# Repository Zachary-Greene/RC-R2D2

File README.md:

# Mini Remote Control R2D2

This repo is for my mini remote control R2D2 project. It includes all the stl files, all the code files, and the f3z (Fusion 360) file. It also includes some Fusion 360 renders and some extra images.

## Prerequisites
All you need is access to a 3D printer, some skills with through-hole soldering and the parts needed.

## Assembly
First solder the components on to the PCB, making sure that they are the right way around and aligned with the silkscreen. Then place the main PCB in the bottom of the body. Place the motors in the mounts in the feet and push the wires through the feet and legs. Then push and glue if necessary the foot to the corresponding leg, eg left foot to left leg. Then push the legs through the holes in the body, making sure to get the in the right orientation, then push the fastening bolt through the holes to secure the legs in the correct position, then glue them. Repeat for the other leg. For the center foot, put the axle through the wheel and glue the axle in place, not the wheel. For the head mechanism, put the motor inside the head stem with the motor lock glued in place under it, then slide the head stem on to the pegs pointing upwards from the body, from there, put the head on to the head stem with some glue. You then plug the wires into the main PCB, turn it on and put the head on top. For the controller, solder the components on and enjoy. (The wheels are lego wheels as they are what I have handy from siblings and will probably be changed in the coming time.)

## Programming
Plug the ATmega328P into a programmer and burn the bootloader if it doesnt already have one. Then upload the corresponding sketch and put the IC in the proper socket.

## Parts
### Main PCB
* ATmega328P Digikey x1
* LD1117V33 (COM-00526) Sparkfun/Core Electronics x1
* NRF24L01 x1
* NPN Transistor (COM-00521) Sparkfun/Core Electronics x12
* 4xAA Battery Holder (PRT-12083) Sparkfun/Core Electronics x1
#### The following is for an optional speaker system
* 0.1uF Ceramic Capacitor (COM-08375) Sparkfun/Core Electronics x1
* 1.25K Ohm Resistor Digikey x1
* 8 Ohm Speaker x1
* DFPlayer Mini (DFR0299) Core Electronics x1

### Controller PCB
* ATmega328P Digikey x1
* LD1117V33 (COM-00526) Sparkfun/Core Electronics x1
* Thumb Joystick (COM-09032) Sparkfun/Core Electronics x2
* NRF24L01 x1
* 4xAA Battery Holder (PRT-12083) Sparkfun/Core Electronics x1

## Renders
.PNG "R2D2 2-3-2 Configuration")
.png "R2D2 2-2 Configuration")

## License
See LICENSE.md

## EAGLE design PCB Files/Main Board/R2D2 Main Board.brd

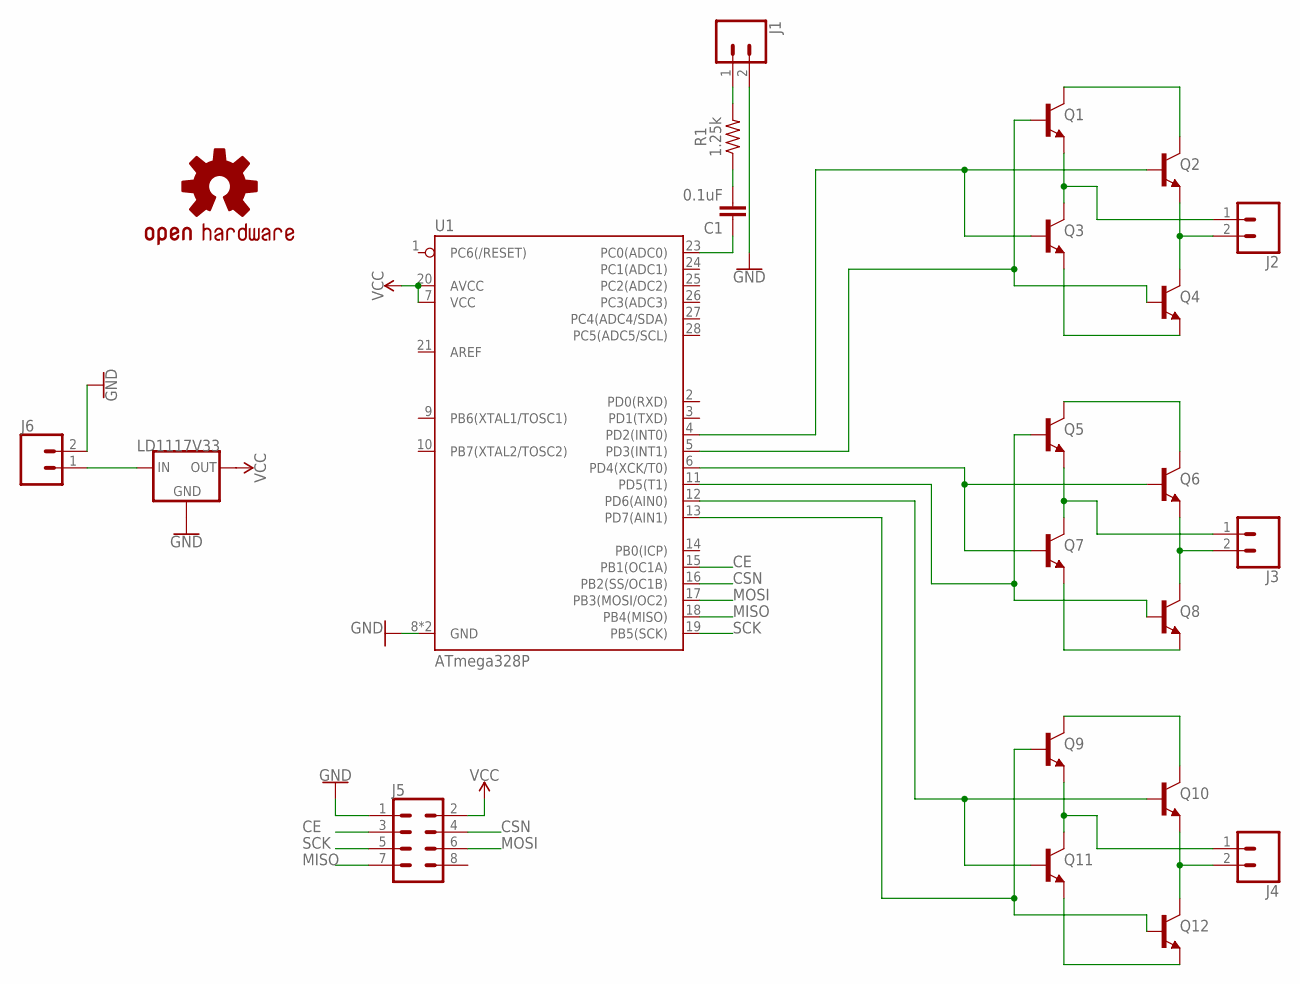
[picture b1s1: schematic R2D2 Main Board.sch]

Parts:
C1: 0.1uF; CAP-PTH-SMALL-KIT
J1, J2, J3, J4, J6: CONN_02; 1X02
J5: CONN_04X2; 2X4
LOGO1: OSHW-LOGOL; OSHW-LOGO-L
Q1, Q2, Q3, Q4, Q5, Q6, Q7, Q8, Q9, Q10, Q11, Q12: 200mA/40V; TO-92
R1: 1.25k; AXIAL-0.3
U1: ATmega328P; DIP28
U$1: LD1117V33; 78XXL

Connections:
CE: J5.3, U1.15 (PB1(OC1A))
CSN: J5.4, U1.16 (PB2(SS/OC1B))
GND: J1.2, J5.1, J6.2, U1.8 (GND), U1.22 (GND), U$1.IN (GND)
MISO: J5.7, U1.18 (PB4(MISO))
MOSI: J5.6, U1.17 (PB3(MOSI/OC2))
unnamed: Q1.3 (C), Q2.3 (C)
unnamed: Q3.1 (E), Q4.1 (E)
unnamed: J2.2, Q2.1 (E), Q4.3 (C)
unnamed: J2.1, Q1.1 (E), Q3.3 (C)
unnamed: Q2.2 (B), Q3.2 (B), U1.4 (PD2(INT0))
unnamed: Q1.2 (B), Q4.2 (B), U1.5 (PD3(INT1))
unnamed: Q5.3 (C), Q6.3 (C)
unnamed: Q7.1 (E), Q8.1 (E)
unnamed: J3.2, Q6.1 (E), Q8.3 (C)
unnamed: J3.1, Q5.1 (E), Q7.3 (C)
unnamed: Q6.2 (B), Q7.2 (B), U1.6 (PD4(XCK/T0))
unnamed: Q5.2 (B), Q8.2 (B), U1.11 (PD5(T1))
unnamed: Q9.3 (C), Q10.3 (C)
unnamed: Q11.1 (E), Q12.1 (E)
unnamed: J4.2, Q10.1 (E), Q12.3 (C)
unnamed: J4.1, Q9.1 (E), Q11.3 (C)
unnamed: Q10.2 (B), Q11.2 (B), U1.12 (PD6(AIN0))
unnamed: Q9.2 (B), Q12.2 (B), U1.13 (PD7(AIN1))
unnamed: C1.1, U1.23 (PC0(ADC0))
unnamed: C1.2, R1.P$1 (1)
unnamed: J1.1, R1.P$2 (2)
SCK: J5.5, U1.19 (PB5(SCK))
VCC: J5.2, U1.7 (VCC), U1.20 (AVCC), U$1.GND (OUT)
VIN: J6.1, U$1.OUT (IN)

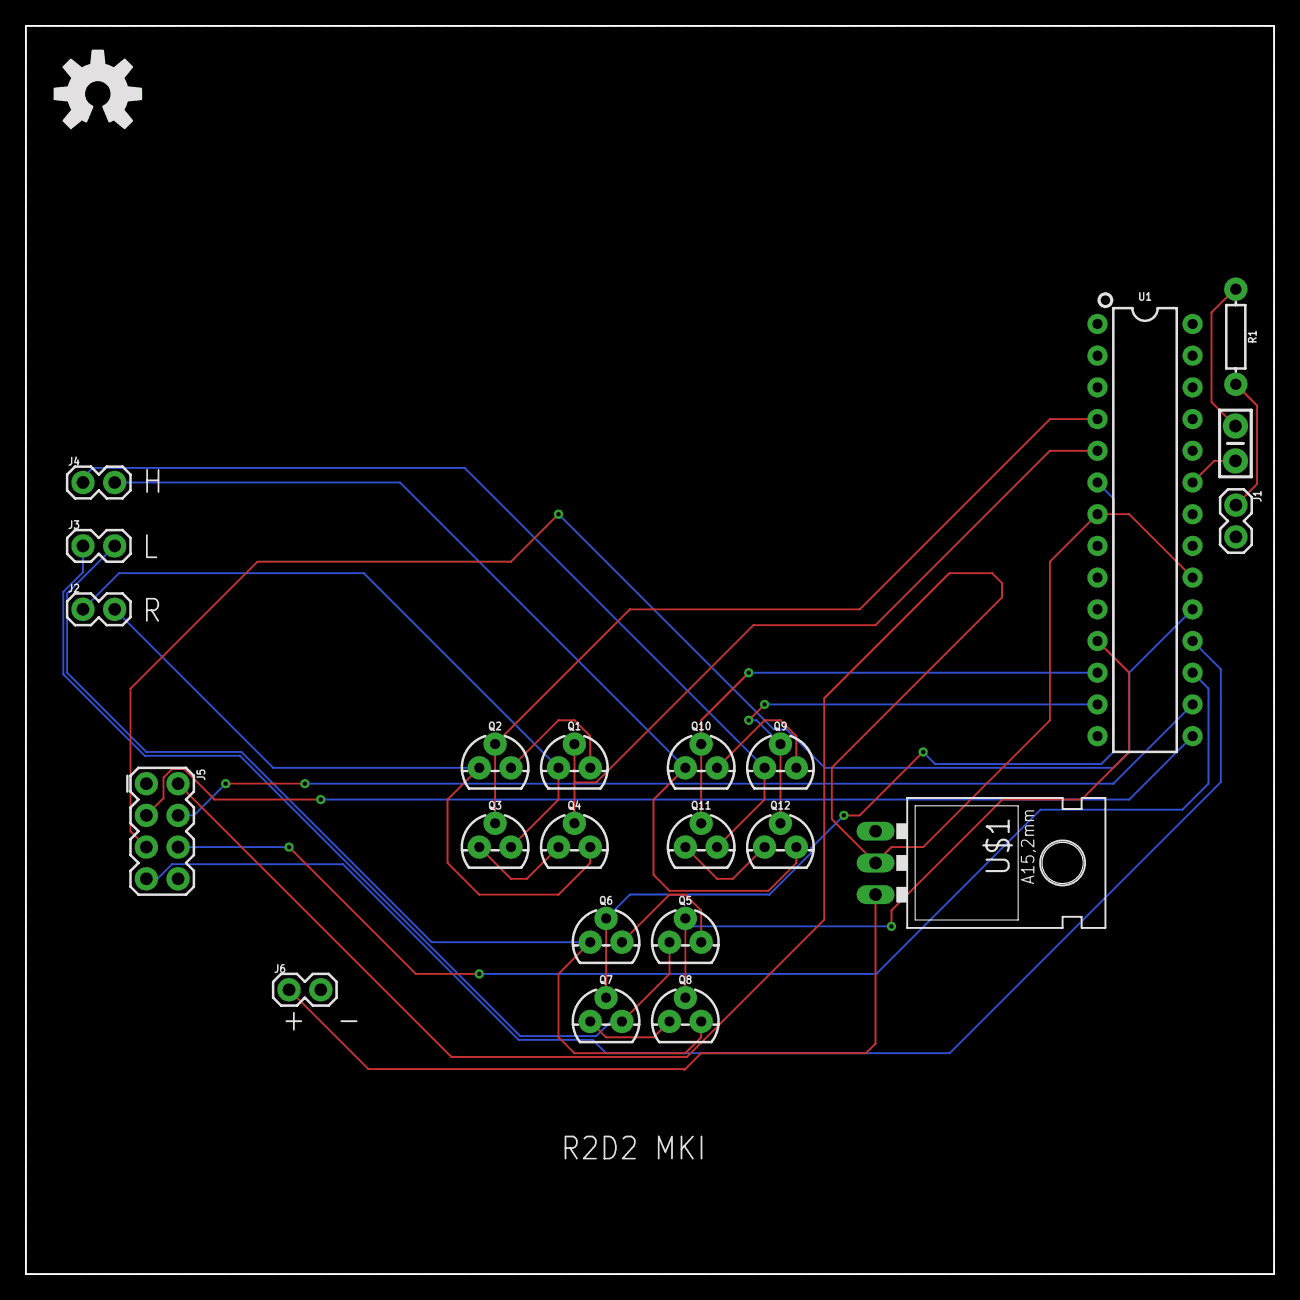
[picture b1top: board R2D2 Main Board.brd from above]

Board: 2 copper layers, 100.0 x 100.0 mm, 23 parts (0 on the bottom side), 29 nets.

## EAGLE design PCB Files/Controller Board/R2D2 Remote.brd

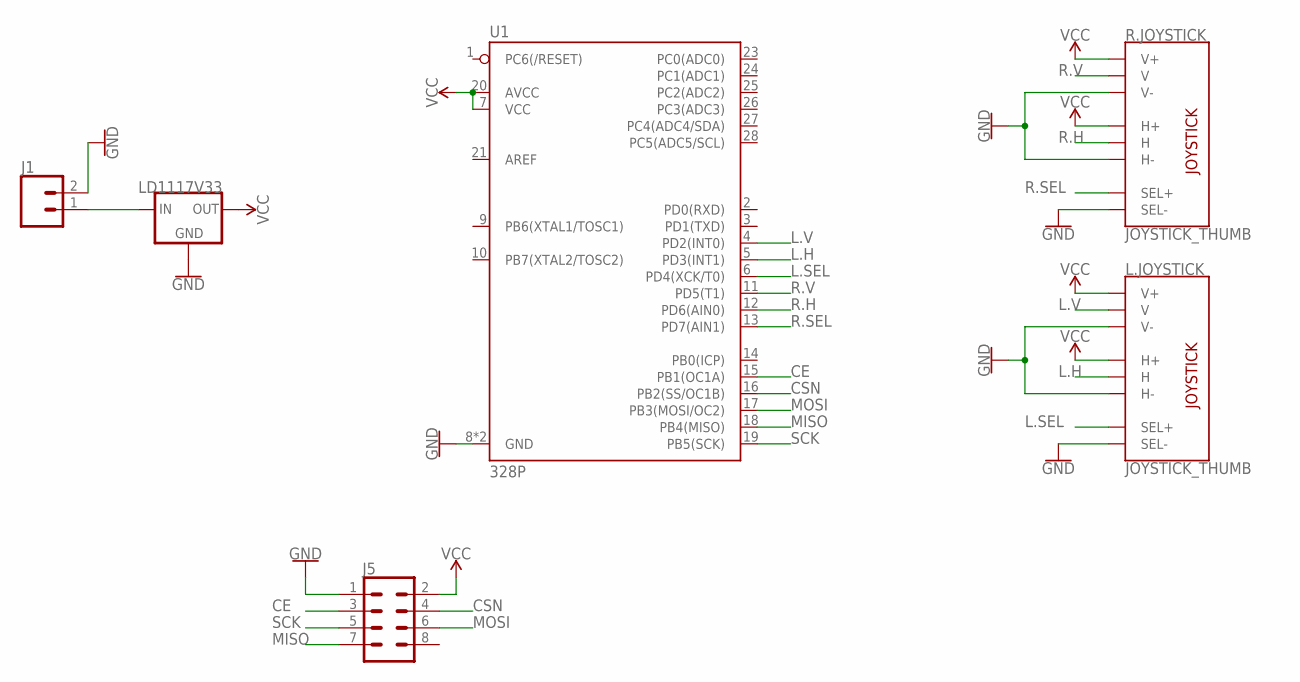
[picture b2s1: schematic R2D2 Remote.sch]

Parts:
J1: CONN_02; 1X02
J5: CONN_04X2; 2X4
L.JOYSTICK: JOYSTICK_THUMB; JOYSTICK
R.JOYSTICK: JOYSTICK_THUMB; JOYSTICK
U1: 328P; DIP28
U$1: LD1117V33; 78XXL

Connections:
CE: J5.3, U1.15 (PB1(OC1A))
CSN: J5.4, U1.16 (PB2(SS/OC1B))
GND: J1.2, J5.1, L.JOYSTICK.B2A (SEL-), L.JOYSTICK.H3 (H-), L.JOYSTICK.V3 (V-), R.JOYSTICK.B2A (SEL-), R.JOYSTICK.H3 (H-), R.JOYSTICK.V3 (V-), U1.8 (GND), U1.22 (GND), U$1.IN (GND)
L.H: L.JOYSTICK.H2 (H), U1.5 (PD3(INT1))
L.SEL: L.JOYSTICK.B1A (SEL+), U1.6 (PD4(XCK/T0))
L.V: L.JOYSTICK.V2 (V), U1.4 (PD2(INT0))
MISO: J5.7, U1.18 (PB4(MISO))
MOSI: J5.6, U1.17 (PB3(MOSI/OC2))
unnamed: J1.1, U$1.OUT (IN)
R.H: R.JOYSTICK.H2 (H), U1.12 (PD6(AIN0))
R.SEL: R.JOYSTICK.B1A (SEL+), U1.13 (PD7(AIN1))
R.V: R.JOYSTICK.V2 (V), U1.11 (PD5(T1))
SCK: J5.5, U1.19 (PB5(SCK))
VCC: J5.2, L.JOYSTICK.H1 (H+), L.JOYSTICK.V1 (V+), R.JOYSTICK.H1 (H+), R.JOYSTICK.V1 (V+), U1.7 (VCC), U1.20 (AVCC), U$1.GND (OUT)

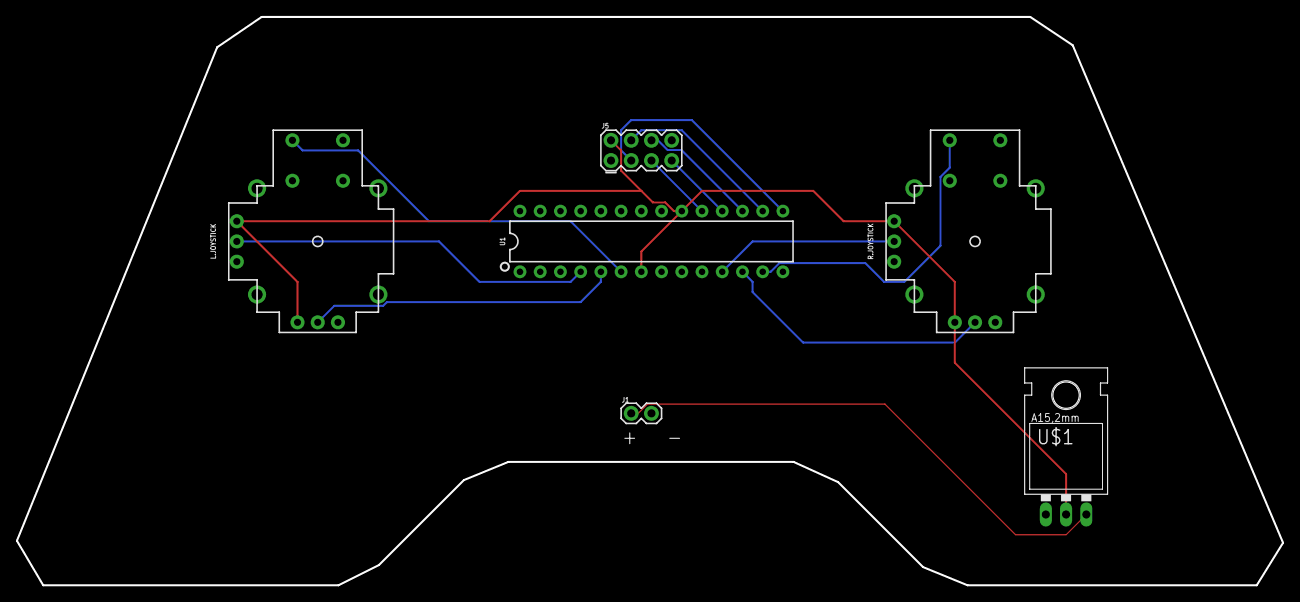
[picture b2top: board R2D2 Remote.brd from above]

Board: 2 copper layers, 159.0 x 71.4 mm, 6 parts (0 on the bottom side), 14 nets.

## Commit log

2020-08-18 Added Images
2020-08-18 Trying adding images
2020-08-18 Added second render
2020-08-18 Added PCB files for main and controller
2020-10-18 Created STL folder
2020-10-18 Add files via upload
    Added all STL files

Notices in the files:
parts and their libraries:
SparkFun-Connectors: Licensing: Creative Commons ShareAlike 4.0 International - https://creativecommons.org/licenses/by-sa/4.0
